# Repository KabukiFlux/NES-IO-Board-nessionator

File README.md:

# NES IO Board "nessionator"

<b align="center">Nessionator, the RGB mod NES output board 
complement for Tim Worthington's NesRGB board</b>

## Table of contents

- [Why](#why)
- [Description](#description)
- [Schematics](#schematics)
- [Install](#install)
- [Pics and final result](#pics-and-final-result)

## Why?

In order to preserve the Nintendo Entertainment System some actions are required like the recapping of the components
cleaning, etc..., one way to ensure compatibility with modern TVs and improve the
image as well is by installing the Tim Worthington's NESRGB board, which interfaces between
the PPU and a CPLD to convert digital into analog signals with multiple palettes.

## Description

This is intended to be a PCB to use with the Tim Worthington's RGB board with a standard NES from regions USA and Europe
without having to do any holes on the case.

This board uses a standard Sega Megadrive 2 RGB cable (Sega Genesis).

No cut is required on the case, so we left the outside of the console untouched.

In the BOM directory there's an interactive BOM with all the required components.

In the gerbers directory we have the gerbers to manufacture the boards.

In the KiCAD folder we can find the KiCAD project itself.

## Schematics

You can find here as well the MD2 cable schematics inside.

## Install

1- Send to manufacture the GERBER board to JLCPCB or other PCB manufacturer.

2- Get the components required, you can see here the Bill Of Materials [BOM](bom/ibom.html)

3- Solder the components.

4- Desolder the RF from the NES but save the header pins connecting the mainboard to the RF board.

5- Follow Tim Wothington's install guide here but do not cut the case!!!: [Guide](https://etim.net.au/nesrgb/installation-nes/) 

6- Follow this soldering guide:

At this stage you should have something like this:

This is a pic with the NESRGB installed for NTSC 60Hz, check the manual for PAL.

Remember to bridge the output 75 ohm resistors as the MD2 cable already has them inside.

* Be careful with the DCDC switching supply IC

### Pics and final result

I know, not the best shot showing the RGB.

<br>

<br>

I'm not responsible
============
And yes, read below, no responsibility taken on bad use.

DISCLAIMER (See Licensing)
==========================
See LICENSE fo more information.

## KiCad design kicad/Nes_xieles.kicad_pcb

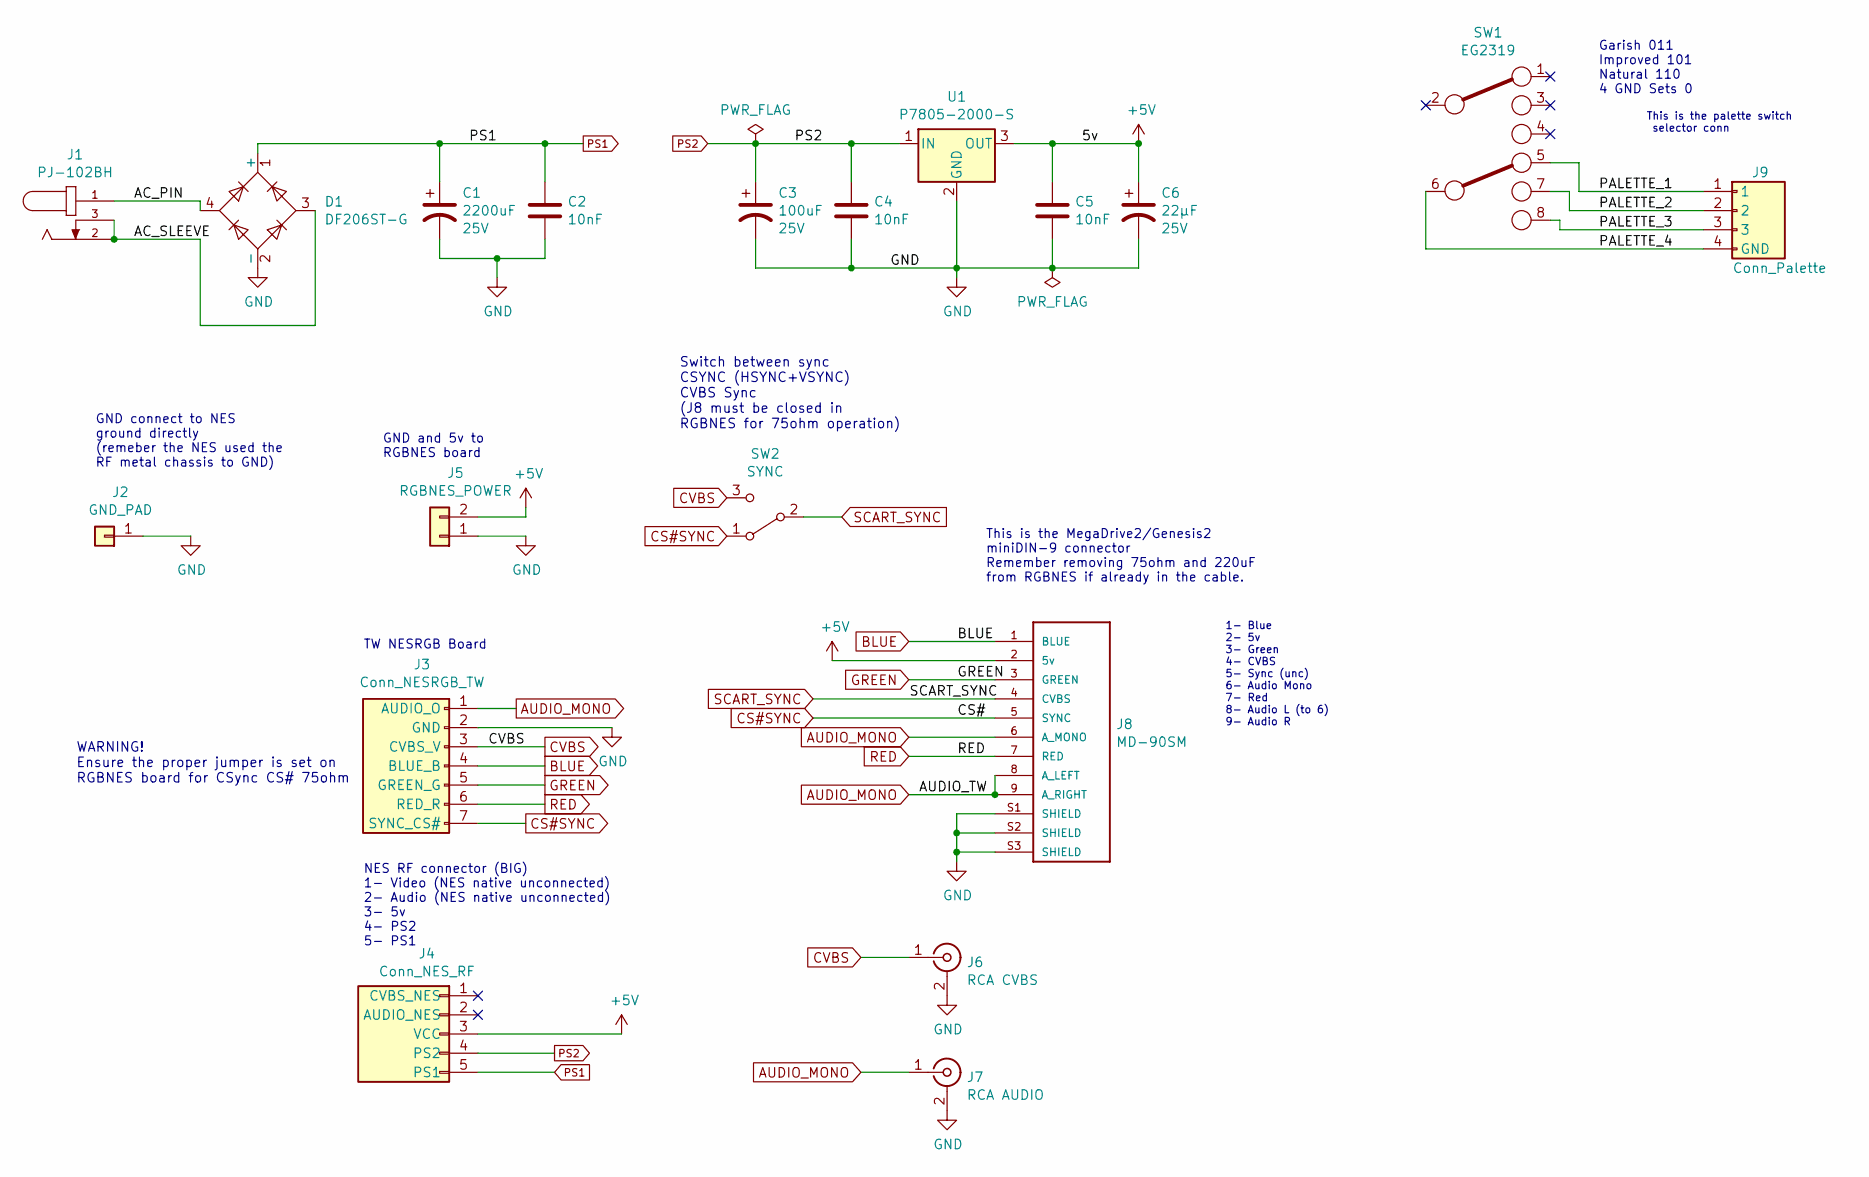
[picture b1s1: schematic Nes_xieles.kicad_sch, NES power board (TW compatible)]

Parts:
C1: 2200uF; CP_Radial_D16.0mm_P7.50mm; Voltage 25V; Mouser REF 647-UKL1E222KHD
C2, C4, C5: 10nF; C_0805_2012Metric_Pad1.15x1.40mm_HandSolder; Mouser REF 80-C0805X103J3G7800
C3: 100uF; CP_EIA-7343-43_Kemet-X_Pad2.25x2.55mm_HandSolder; Voltage 25V; Mouser REF 80-T495X107K25ATE150
C6: 22μF; CP_EIA-6032-28_Kemet-C_Pad2.25x2.35mm_HandSolder; Voltage 25V; Mouser REF 80-T491C226K025
D1: DF206ST-G; Diode_Bridge_Vishay_DFS; Mouser REF 750-DF206ST-G
J1: PJ-102BH; BarrelJack_NES; Mouser REF 490-PJ-102BH
J2: GND_PAD; Pin_D1.3mm_L11.0mm
J3: Conn_NESRGB_TW; PinHeader_1x07_P2.54mm_Vertical
J4: Conn_NES_RF; RF_CONN_NES
J5: RGBNES_POWER; PinHeader_1x02_P2.54mm_Vertical
J6: RCA CVBS; CUI_RCJ-043; Mouser REF 490-RCJ-043
J7: RCA AUDIO; CUI_RCJ-043; Mouser REF 490-RCJ-043
J8: MD-90SM; CUI_MD-90SM; Mouser REF 490-MD-90SM
J9: Conn_Palette; PinHeader_1x04_P2.54mm_Vertical
SW1: EG2319; Mouser REF 612-EG2319
SW2: SYNC; SW_SPDT_PCM12; Mouser REF 611-PCM12SMTR
U1: P7805-2000-S; 3-SIP_Module_V7805-500; Mouser REF 490-P7805-2000-S

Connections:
+5V: C5.1, C6.1, J4.3 (VCC), J5.2, J8.2 (5v), U1.3 (OUT)
/AC_PIN: D1.4, J1.1
/AC_SLEEVE: D1.3, J1.2, J1.3
/PALETTE_1: J9.1, SW1.5
/PALETTE_2: J9.2, SW1.7
/PALETTE_3: J9.3, SW1.8
/PALETTE_4: J9.4 (GND), SW1.6
AUDIO_MONO: J3.1 (AUDIO_O), J7.1 (In), J8.6 (A_MONO), J8.8 (A_LEFT), J8.9 (A_RIGHT)
BLUE: J3.4 (BLUE_B), J8.1 (BLUE)
CS#SYNC: J3.7 (SYNC_CS#), J8.5 (SYNC), SW2.1 (A)
CVBS: J3.3 (CVBS_V), J6.1 (In), SW2.3 (C)
GND: C1.2, C2.2, C3.2, C4.2, C5.2, C6.2, D1.2 (-), J2.1, J3.2 (GND), J5.1, J6.2 (Ext), J7.2 (Ext), J8.S1 (SHIELD), J8.S2 (SHIELD), J8.S3 (SHIELD), U1.2 (GND)
GREEN: J3.5 (GREEN_G), J8.3 (GREEN)
PS1: C1.1, C2.1, D1.1 (+), J4.5 (PS1)
PS2: C3.1, C4.1, J4.4 (PS2), U1.1 (IN)
RED: J3.6 (RED_R), J8.7 (RED)
SCART_SYNC: J8.4 (CVBS), SW2.2 (B)

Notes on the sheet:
GND connect to NES ground directly (remeber the NES used the RF metal chassis to GND)
TW NESRGB Board
1- Blue 2- 5v 3- Green 4- CVBS 5- Sync (unc) 6- Audio Mono 7- Red 8- Audio L (to 6) 9- Audio R
GND and 5v to RGBNES board
Garish 011 Improved 101 Natural 110 4 GND Sets 0
NES RF connector (BIG) 1- Video (NES native unconnected) 2- Audio (NES native unconnected) 3- 5v 4- PS2 5- PS1
This is the palette switch selector conn
This is the MegaDrive2/Genesis2 miniDIN-9 connector Remember removing 75ohm and 220uF from RGBNES if already in the cable.
WARNING! Ensure the proper jumper is set on RGBNES board for CSync CS# 75ohm
Switch between sync CSYNC (HSYNC+VSYNC) CVBS Sync (J8 must be closed in RGBNES for 75ohm operation)

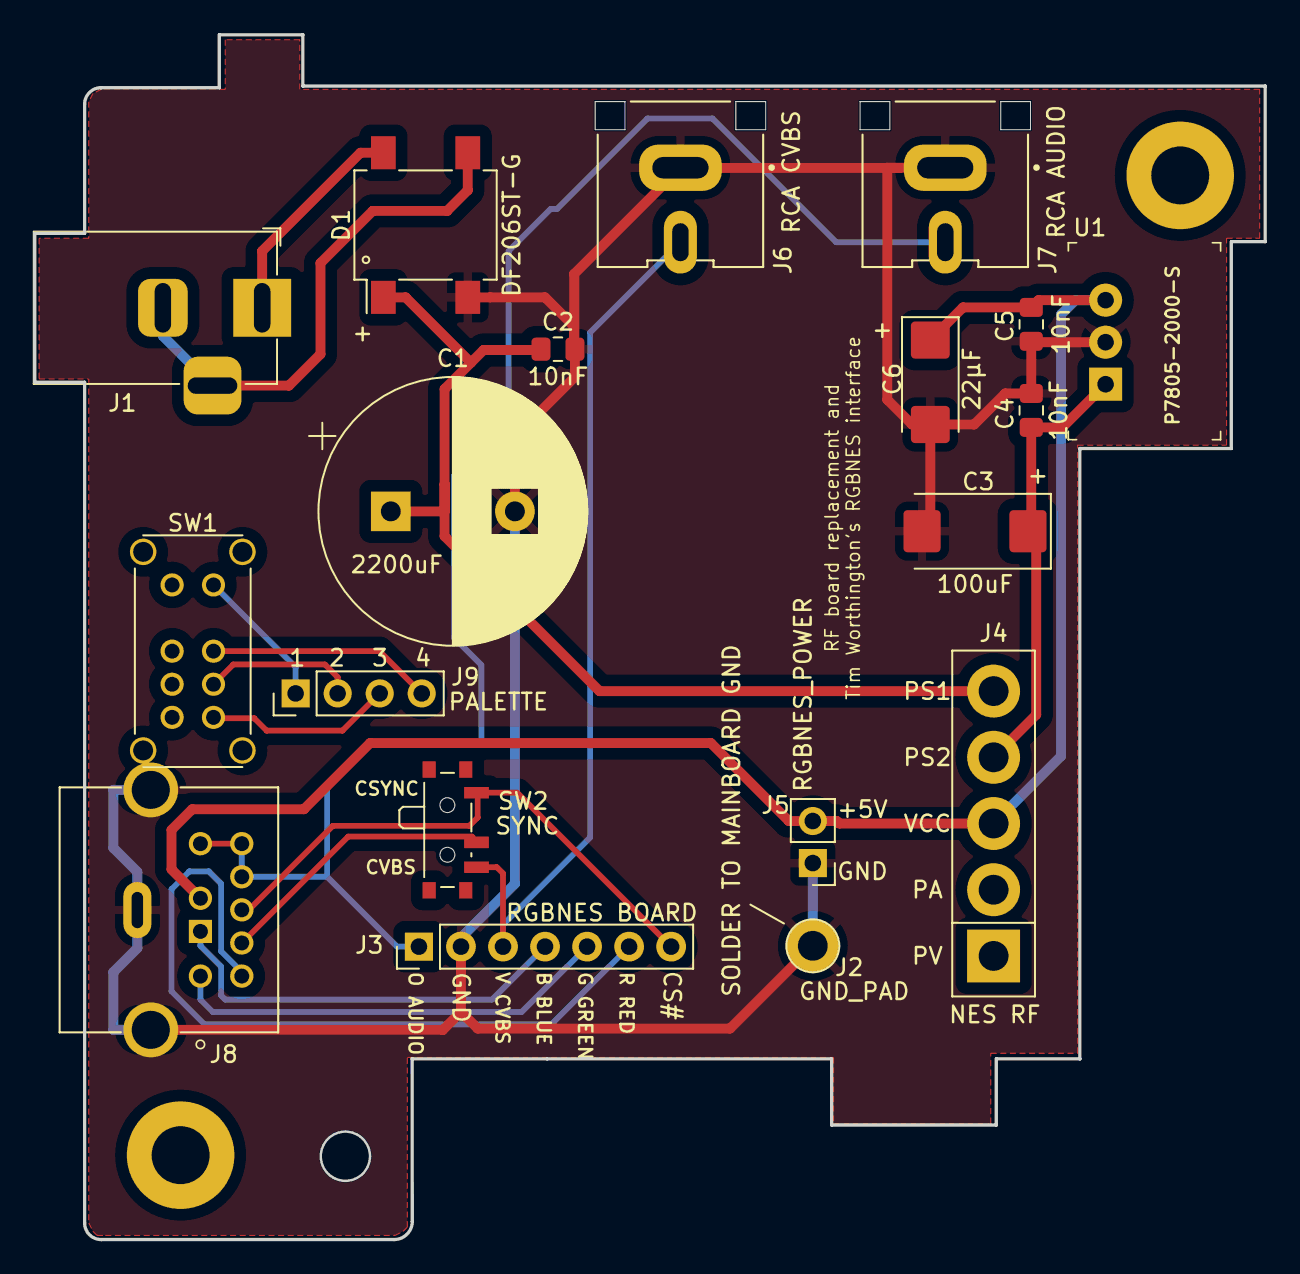
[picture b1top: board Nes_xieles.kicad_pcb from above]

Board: 2 copper layers, 74.3 x 72.8 mm, 21 parts (0 on the bottom side), 17 nets.

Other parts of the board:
MH1, MH2: MountingHole_3.5mm_Pad

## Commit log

2023-09-14 Project uploaded, just try it!
2023-10-30 Update LICENSE
